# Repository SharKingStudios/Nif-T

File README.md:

# Nif-T - An all in one smart home automation board

### A No-Nonsense Ethernet + PoE Smart-Home Controller

---

## Renders  
*Visuals because everyone loves eye candy.*

> *The middle ground planes are hidden in the PCB Routing render*

---

## BOM  
All the silicon, magnetics, and clicky-relay goodness live **[here](/BOM.csv)**.

**Main characters:**
- **MCU:** ESP32-WROOM-32E
- **Ethernet PHY:** LAN8720A (RMII, external 50 MHz oscillator)
- **Power over Ethernet:** IEEE 802.3af PoE (on-board PD + isolation)
- **Relays:** 8× PCB-mount power relays
- **RGB LEDs:** 10× SK6812 Mini
- **Buzzer:** On-board piezo
- **User Input:** Programmable user button
- **Connectivity:** Ethernet (primary), USB-UART for flashing/debug
- **Power:** PoE-powered with on-board regulation for ESP32 + peripherals
- **Misc:** Boot circuitry, reset logic, pull-ups, decoupling, and other necessary magic

(See `BOM.md` for full part values, footprints, and sourcing.)

---

## What is this?

**Nif-T** is a **wired smart-home automation controller** built around an **ESP32-WROOM-32E**, designed to be the thing that actually flips real switches when you ask your house to do something.

It’s meant for:
- **Lights**
- **Outlets**
- **Relays**
- **Buzzers**
- **Addressable LEDs**
- And other “turn this on when I say so” tasks

Unlike a lot of Wi-Fi-only smart devices, **Nif-T speaks Ethernet** — and it can be powered over the same cable using **PoE**. One cable in, automation out.

At a high level, Nif-T:
- Exposes **physical relays and LEDs**
- Talks to **Home Assistant**
- Which then talks to **Google Home**
- So you can say things like:

> *“Hey Google, turn on the big light.”*

…and something actually happens.

---

## Features

### Relay Control
- **8× independent relay outputs**
- Designed for:
  - Lighting circuits
  - Power control
  - Low-voltage automation tasks
- Each relay is individually addressable via firmware
- Can be controlled via:
  - MQTT
  - Home Assistant
  - Google Home (through HA)

*(Please don’t hot-switch mains unless you know what you’re doing.)*

---

### Ethernet + PoE
Because reliability matters — and wall warts are annoying.

- **LAN8720A Ethernet PHY**
  - RMII interface
  - Dedicated 50 MHz oscillator on the PHY
- **IEEE 802.3af Power over Ethernet**
  - Single-cable power + data
  - On-board PD controller and isolation
  - Clean DC rails generated locally
- No Wi-Fi congestion
- No random disconnects
- No external power brick required

Plug in Ethernet. That’s it.

---

### RGB Status LEDs
Because silent boards are boring.

- **10× SK6812 Mini (GRBW) LEDs**
- Can indicate:
  - Network status
  - MQTT / Home Assistant connection
  - Relay activity
  - Boot / error states
  - Or just run rainbow animations for morale
- Fully firmware-controlled

---

### Buttons & Feedback
- **User button**
  - Can be mapped to:
    - Toggle a relay
    - Enter config mode
    - Trigger a scene
- **On-board buzzer**
  - Boot beeps
  - Error alerts
  - Confirmation chirps
  - Mildly annoying sounds (optional but encouraged)

---

## Connectivity & IO

- **ESP32-WROOM-32E**
  - Dual-core MCU
  - Plenty of GPIO for:
    - Relays
    - LEDs
    - Buttons
    - Buzzers
- **USB-UART**
  - Firmware flashing
  - Serial debugging
- **Screw terminals**
  - For relays and power connections that shouldn’t wiggle loose

---

## Pin Highlights (High-Level)

| Function        | Notes                                   |
|-----------------|------------------------------------------|
| Relays          | 8× GPIO-controlled outputs               |
| LED Data        | SK6812 GRBW strip (10 LEDs)              |
| Ethernet RMII   | LAN8720A w/ external 50 MHz oscillator   |
| PoE Input       | IEEE 802.3af compliant                   |
| User Button     | Input-only GPIO (external pull-ups)      |
| Buzzer          | GPIO-driven piezo output                 |

*(See schematic for full pin mapping and signal names.)*

---

## How It Works

At a high level:

1. **You plug in Ethernet** (which also provides power via PoE)
2. The **PoE PD negotiates power** and generates isolated DC rails
3. The **ESP32 boots** and brings up Ethernet
4. It connects to:
   - An **MQTT broker** (usually Home Assistant)
5. Home Assistant:
   - Discovers Nif-T automatically
   - Exposes relays and LEDs as entities
6. Google Home talks to Home Assistant
7. You talk to Google
8. Nif-T clicks relays and blinks LEDs

---

## Example Use Cases

- “Hey Google, turn on the **workbench lights**”
- “Turn off **everything downstairs**”
- LED status strip that shows:
  - Green = online
  - Red = offline
  - Blue = updating
- Physical button toggles a relay *and* triggers a Home Assistant scene
- Buzzer chirps when automations fire (or silently if you prefer)

---

## Why?

Because:
- Wi-Fi smart plugs are flaky
- Ethernet is king
- PoE makes installs clean
- And sometimes you just want a **solid, hackable, relay board** that plays nicely with modern home automation

Nif-T exists to be:
- Boring in the best way
- Reliable
- Predictable
- And extremely easy to integrate into a real automation stack

---

## Contribute

Ideas, improvements, and constructive roasting welcome.

- Open an **issue**
- Submit a **PR**
- Suggest features
- Argue about relay counts

---

## Disclaimer

This project is open-source, built for fun, and tested only in theory.

If you:
- Wire mains incorrectly
- Ignore clearance rules
- Overload a relay
- Or let the magic smoke out

That’s on you.

Be careful, be smart, and enjoy having a house that actually listens.

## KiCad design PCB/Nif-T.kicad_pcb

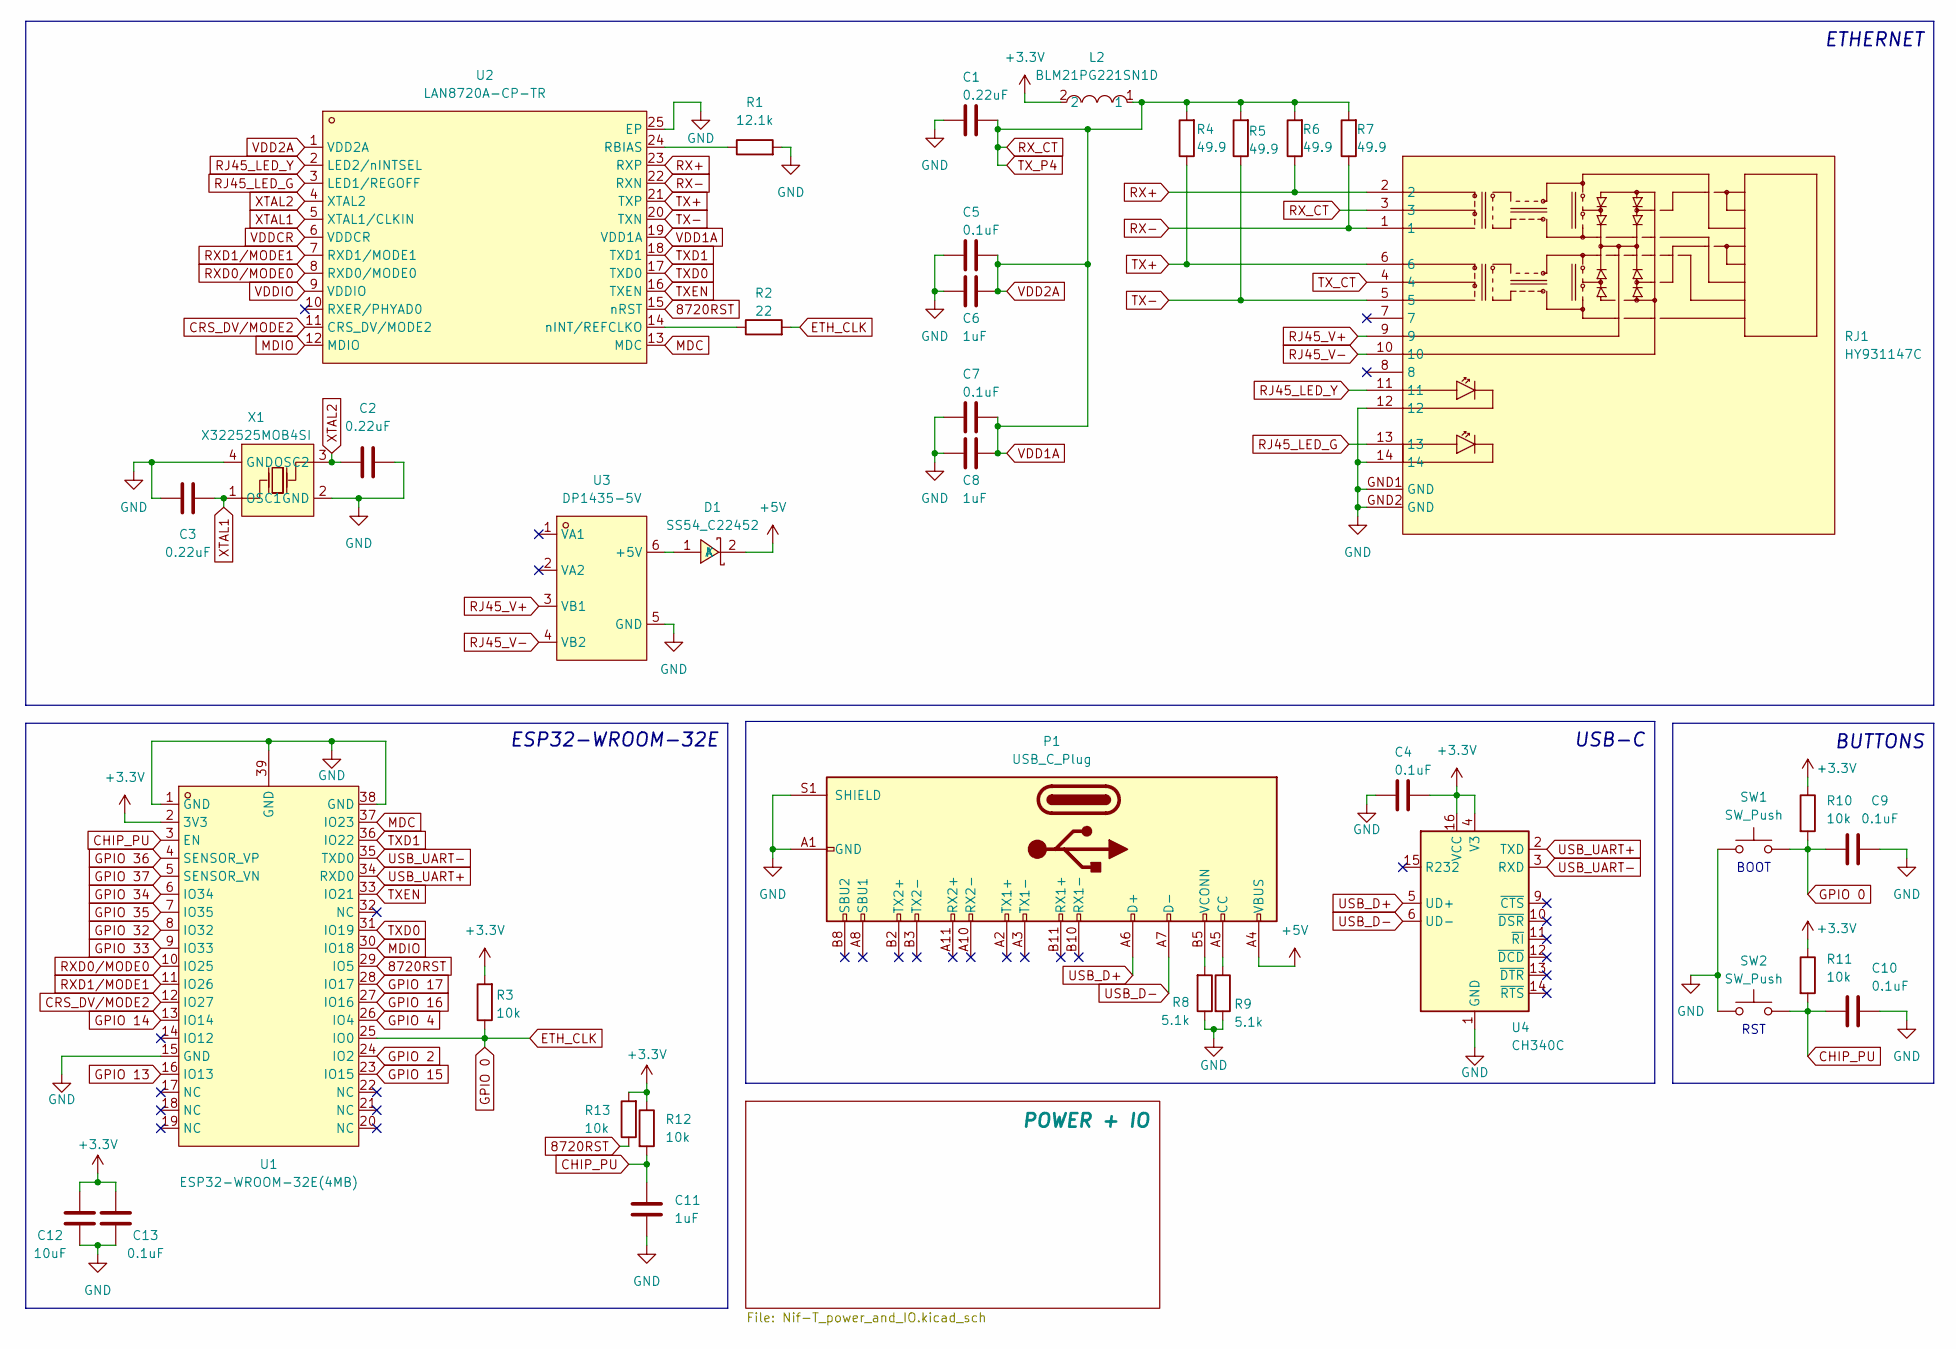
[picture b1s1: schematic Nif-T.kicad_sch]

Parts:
C1, C2, C3: 0.22uF; C0805
C4, C5, C7, C9, C10, C13: 0.1uF; C0805
C6, C8, C11: 1uF; C0805
C12: 10uF; C0805
D1: SS54_C22452; SMA_L4.4-W2.8-LS5.4-R-RD; LCSC Part C22452
L2: BLM21PG221SN1D; L0805; LCSC Part C85840
P1: USB_C_Plug; USB-C_SMD-TYPE-C-31-M-12
R1: 12.1k; R0805
R2: 22; R0805
R3, R10, R11, R12, R13: 10k; R0805
R4, R5, R6, R7: 49.9; R0805
R8, R9: 5.1k; R0805
RJ1: HY931147C; RJ45-TH_HY931147C; LCSC Part C91754
SW1, SW2: SW_Push; SW-SMD_L3.9-W3.0-P4.45
U1: ESP32-WROOM-32E(4MB); WIFI-SMD_ESP32-WROOM-32E; LCSC Part C701341
U2: LAN8720A-CP-TR; QFN-24_L4.0-W4.0-P0.50-BL-EP2.6; LCSC Part C45223
U3: DP1435-5V; PWRM-TH_DP1435-XX; LCSC Part C5380097
U4: CH340C; SOIC-16_3.9x9.9mm_P1.27mm
X1: X322525MOB4SI; CRYSTAL-SMD_4P-L3.2-W2.5-BL; LCSC Part C9006

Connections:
8720RST: R13.1, U1.29 (IO5), U2.15 (nRST)
+3.3V: C4.1, C12.2, C13.2, L2.2, R3.2, R10.1, R11.1, R12.1, R13.2, U1.2 (3V3), U4.4 (V3), U4.16 (VCC); also elsewhere on the board
+5V: D1.2 (K), P1.A4 (VBUS), P1.A9 (VBUS), P1.B4 (VBUS), P1.B9 (VBUS); also elsewhere on the board
CHIP_PU: C10.1, C11.1, R11.2, R12.2, SW2.1, U1.3 (EN)
CRS_DV/MODE2: U1.12 (IO27), U2.11 (CRS_DV/MODE2)
ETH_CLK: C9.1, R2.2, R3.1, R10.2, SW1.1, U1.25 (IO0)
GND: C1.2, C2.2, C3.1, C4.2, C5.2, C6.2, C7.2, C8.2, C9.2, C10.2, C11.2, C12.1, C13.1, P1.A1 (GND), P1.A12 (GND), P1.B1 (GND), P1.B12 (GND), P1.S1 (SHIELD), R1.2, R8.1, R9.2, RJ1.12, RJ1.14, RJ1.GND1 (GND), RJ1.GND2 (GND), SW1.2, SW2.2, U1.1 (GND), U1.15 (GND), U1.38 (GND), U1.39 (GND), U2.25 (EP), U3.5 (GND), U4.1 (GND), X1.2 (GND), X1.4 (GND); also elsewhere on the board
GPIO 2: U1.24 (IO2); also elsewhere on the board
GPIO 4: U1.26 (IO4); also elsewhere on the board
GPIO 13: U1.16 (IO13); also elsewhere on the board
GPIO 14: U1.13 (IO14); also elsewhere on the board
GPIO 15: U1.23 (IO15); also elsewhere on the board
GPIO 16: U1.27 (IO16); also elsewhere on the board
GPIO 17: U1.28 (IO17); also elsewhere on the board
GPIO 32: U1.8 (IO32); also elsewhere on the board
GPIO 33: U1.9 (IO33); also elsewhere on the board
GPIO 34: U1.6 (IO34); also elsewhere on the board
GPIO 35: U1.7 (IO35); also elsewhere on the board
GPIO 36: U1.4 (SENSOR_VP); also elsewhere on the board
GPIO 37: U1.5 (SENSOR_VN); also elsewhere on the board
MDC: U1.37 (IO23), U2.13 (MDC)
MDIO: U1.30 (IO18), U2.12 (MDIO)
unnamed: D1.1 (A), U3.6 (+5V)
unnamed: P1.A5 (CC), R9.1
unnamed: P1.B5 (VCONN), R8.2
unnamed: R1.1, U2.24 (RBIAS)
unnamed: R2.1, U2.14 (nINT/REFCLKO)
RJ45_LED_G: RJ1.13, U2.3 (LED1/REGOFF)
RJ45_LED_Y: RJ1.11, U2.2 (LED2/nINTSEL)
RJ45_V+: RJ1.9, U3.3 (VB1)
RJ45_V-: RJ1.10, U3.4 (VB2)
RX+: R6.1, RJ1.2, U2.23 (RXP)
RX-: R7.1, RJ1.1, U2.22 (RXN)
RXD0/MODE0: U1.10 (IO25), U2.8 (RXD0/MODE0)
RXD1/MODE1: U1.11 (IO26), U2.7 (RXD1/MODE1)
RX_CT: C1.1, C5.1, C6.1, C7.1, C8.1, L2.1, R4.2, R5.2, R6.2, R7.2, RJ1.3, U2.1 (VDD2A), U2.19 (VDD1A)
TX+: R4.1, RJ1.6, U2.21 (TXP)
TX-: R5.1, RJ1.5, U2.20 (TXN)
TXD0: U1.31 (IO19), U2.17 (TXD0)
TXD1: U1.36 (IO22), U2.18 (TXD1)
TXEN: U1.33 (IO21), U2.16 (TXEN)
TX_CT: RJ1.4
USB_D+: P1.A6 (D+), U4.5 (UD+)
USB_D-: P1.A7 (D-), U4.6 (UD-)
USB_UART+: U1.34 (RXD0), U4.2 (TXD)
USB_UART-: U1.35 (TXD0), U4.3 (RXD)
VDDCR: U2.6 (VDDCR)
VDDIO: U2.9 (VDDIO)
XTAL1: C3.2, U2.5 (XTAL1/CLKIN), X1.1 (OSC1)
XTAL2: C2.1, U2.4 (XTAL2), X1.3 (OSC2)

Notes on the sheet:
BOOT
ESP32-WROOM-32E
ETHERNET
RST
USB-C
BUTTONS

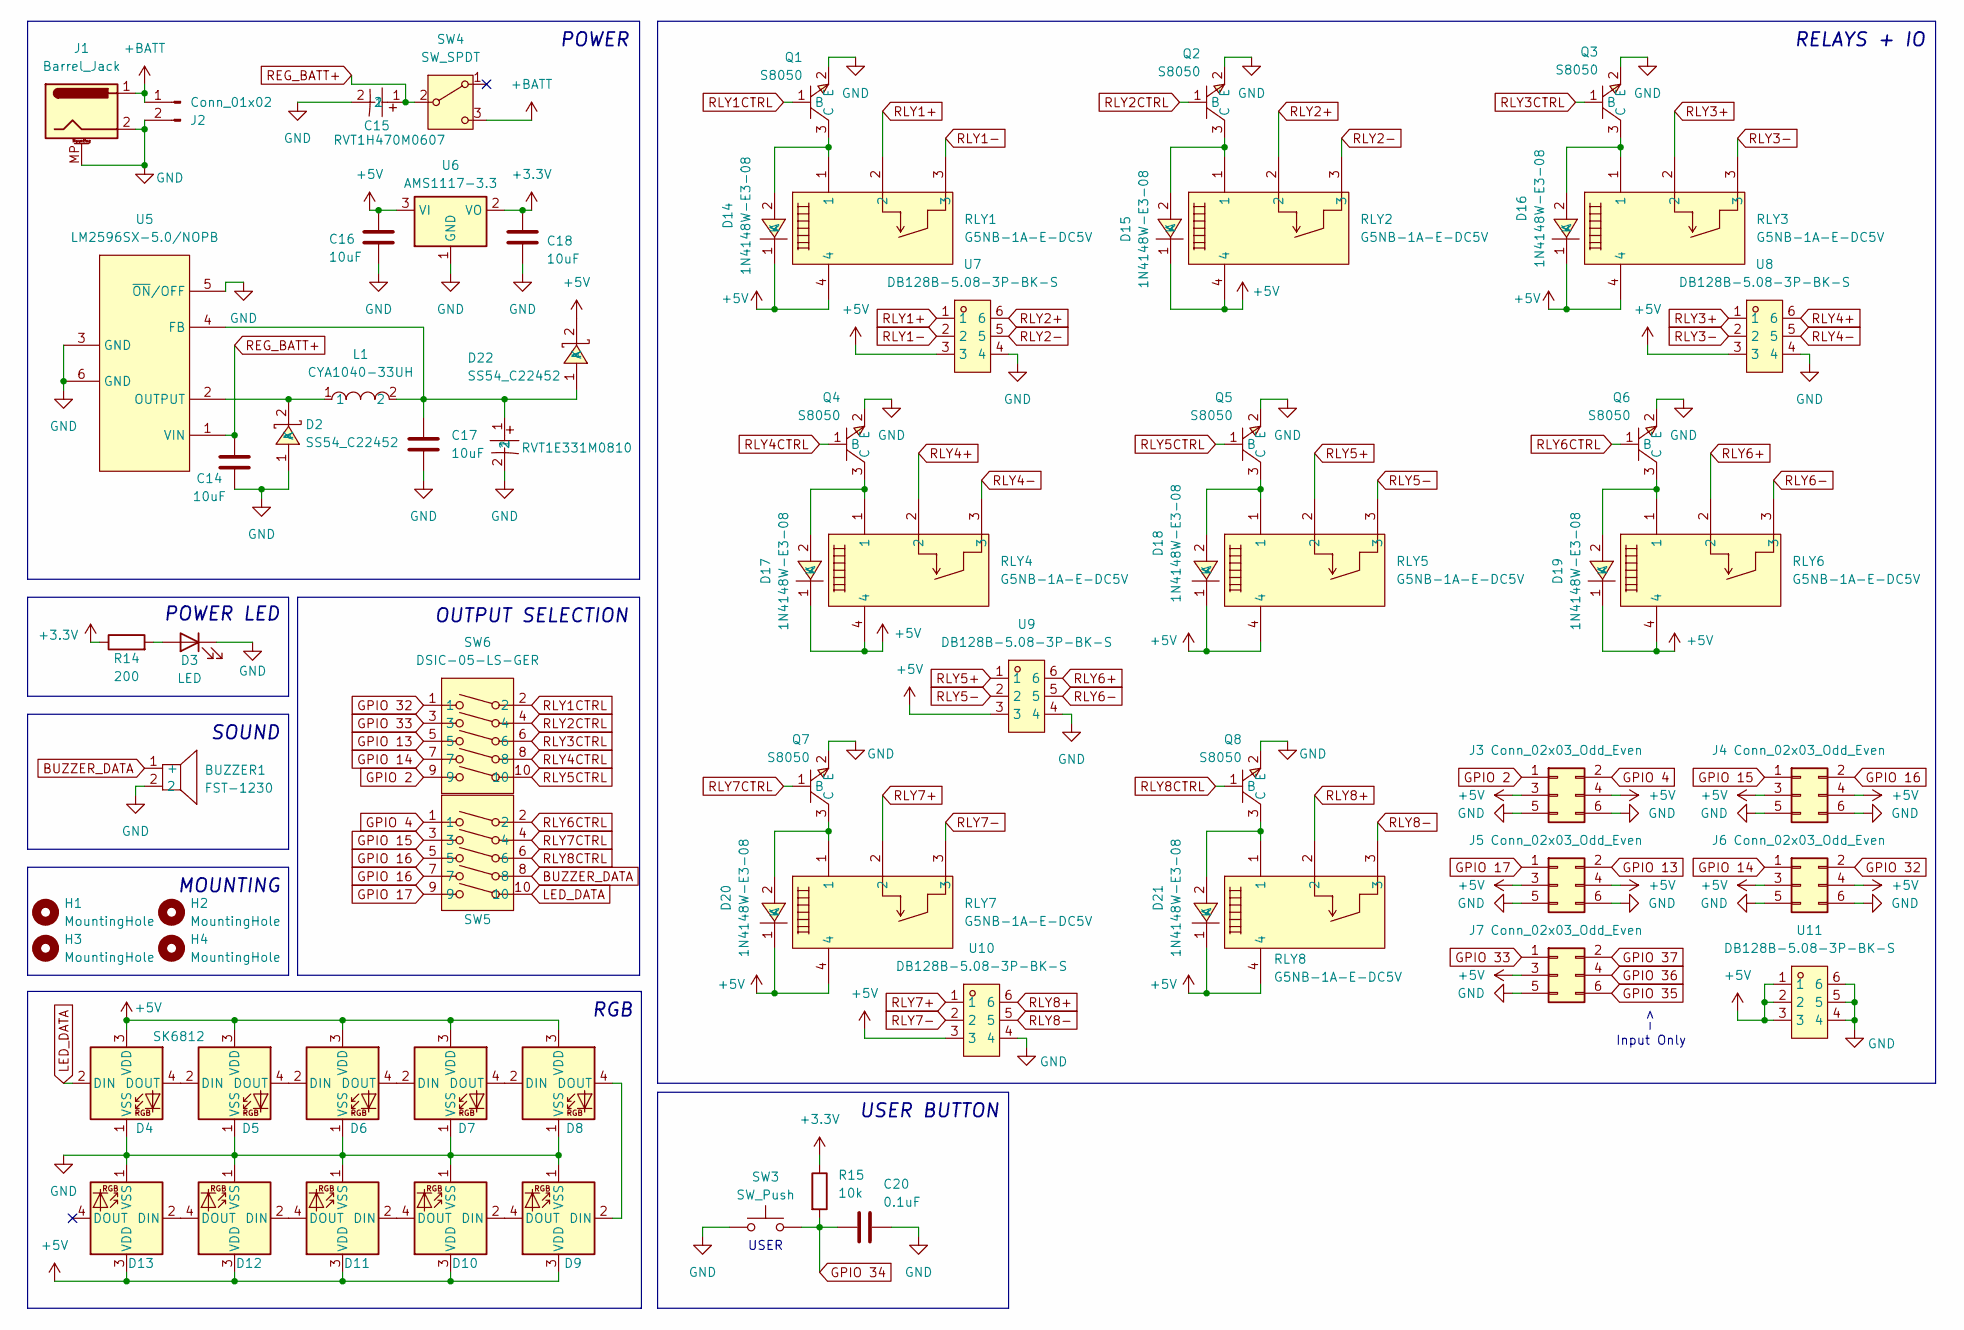
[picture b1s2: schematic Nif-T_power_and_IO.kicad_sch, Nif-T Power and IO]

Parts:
BUZZER1: FST-1230; BUZ-SMD_L12.0-W12.0_FUET-1230; LCSC Part C391037
C14, C16, C17, C18: 10uF; C0805
C15: RVT1H470M0607; CAP-SMD_BD6.3-L6.6-W6.6-LS7.6-FD; LCSC Part C72523
C19: RVT1E331M0810; CAP-SMD_BD8.0-L8.3-W8.3-LS9.3-FD-1; LCSC Part C335985
C20: 0.1uF; C0805
D2, D22: SS54_C22452; SMA_L4.4-W2.8-LS5.4-R-RD; LCSC Part C22452
D3: LED; LED0805-RD
D4, D5, D6, D7, D8, D9, D10, D11, D12, D13: SK6812; LED_SK6812_PLCC4_5.0x5.0mm_P3.2mm
D14, D15, D16, D17, D18, D19, D20, D21: 1N4148W-E3-08; SOD-123_L2.8-W1.8-LS3.7-RD; LCSC Part C241939
H1, H2, H3, H4: MountingHole; MountingHole_3.2mm_M3_Pad_Via
J1: Barrel_Jack; DC-IN-TH_DC-005-A200
J2: Conn_01x02; CONN-TH_P5.00_KF301-5.0-2P
J3, J4, J5, J6, J7: Conn_02x03_Odd_Even; HDR-SMD_6P-P2.54-V
L1: CYA1040-33UH; IND-SMD_L11.6-W10.1; LCSC Part C6364680
Q1, Q2, Q3, Q4, Q5, Q6, Q7, Q8: S8050; SOT-23-3_L2.9-W1.3-P1.90-LS2.4-BR; LCSC Part C916390
R14: 200; R0805
R15: 10k; R0805
RLY1, RLY2, RLY3, RLY4, RLY5, RLY6, RLY7, RLY8: G5NB-1A-E-DC5V; RELAY-TH_G5NB-1A-E-DCXX; LCSC Part C48746
SW3: SW_Push; SW-SMD_L3.9-W3.0-P4.45
SW4: SW_SPDT; SW-SMD_MST-12D18G4-SPDT-SLIDE-SWITCH
SW5, SW6: DSIC-05-LS-GER; SW-SMD_DSIC-05-LS-GER; LCSC Part C7471367
U5: LM2596SX-5.0/NOPB; TO-263-5_L10.2-W8.9-P1.70-TL; LCSC Part C10002
U6: AMS1117-3.3; SOT-223-3_TabPin2
U7, U8, U9, U10, U11: DB128B-5.08-3P-BK-S; CONN-TH_DB128B-5.08-3P-XX-S; LCSC Part C500038

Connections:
+3.3V: C18.1, R14.1, R15.1, U6.2 (VO); also elsewhere on the board
+5V: C16.1, D4.3 (VDD), D5.3 (VDD), D6.3 (VDD), D7.3 (VDD), D8.3 (VDD), D9.3 (VDD), D10.3 (VDD), D11.3 (VDD), D12.3 (VDD), D13.3 (VDD), D14.1 (K), D15.1 (K), D16.1 (K), D17.1 (K), D18.1 (K), D19.1 (K), D20.1 (K), D21.1 (K), D22.2 (K), J3.3, J3.4, J4.3, J4.4, J5.3, J5.4, J6.3, J6.4, J7.3, RLY1.4, RLY2.4, RLY3.4, RLY4.4, RLY5.4, RLY6.4, RLY7.4, RLY8.4, U6.3 (VI), U7.3, U8.3, U9.3, U10.3, U11.1, U11.2, U11.3; also elsewhere on the board
+BATT: J1.1, J2.1, SW4.3 (C)
BUZZER_DATA: BUZZER1.1 (+), SW5.8
GND: BUZZER1.2, C14.1, C15.2, C16.2, C17.2, C18.2, C19.2, C20.2, D2.1 (A), D3.1 (K), D4.1 (VSS), D5.1 (VSS), D6.1 (VSS), D7.1 (VSS), D8.1 (VSS), D9.1 (VSS), D10.1 (VSS), D11.1 (VSS), D12.1 (VSS), D13.1 (VSS), J1.2, J1.MP (MountPin), J2.2, J3.5, J3.6, J4.5, J4.6, J5.5, J5.6, J6.5, J6.6, J7.5, Q1.2 (E), Q2.2 (E), Q3.2 (E), Q4.2 (E), Q5.2 (E), Q6.2 (E), Q7.2 (E), Q8.2 (E), SW3.2, U5.3 (GND), U5.5 (~ON/OFF), U5.6 (GND), U6.1 (GND), U7.4, U8.4, U9.4, U10.4, U11.4, U11.5, U11.6; also elsewhere on the board
GPIO 2: J3.1, SW6.9; also elsewhere on the board
GPIO 4: J3.2, SW5.1; also elsewhere on the board
GPIO 13: J5.2, SW6.5; also elsewhere on the board
GPIO 14: J6.1, SW6.7; also elsewhere on the board
GPIO 15: J4.1, SW5.3; also elsewhere on the board
GPIO 16: J4.2, SW5.5, SW5.7; also elsewhere on the board
GPIO 17: J5.1, SW5.9; also elsewhere on the board
GPIO 32: J6.2, SW6.1; also elsewhere on the board
GPIO 33: J7.1, SW6.3; also elsewhere on the board
GPIO 34: C20.1, R15.2, SW3.1; also elsewhere on the board
GPIO 35: J7.6; also elsewhere on the board
GPIO 36: J7.4; also elsewhere on the board
GPIO 37: J7.2; also elsewhere on the board
LED_DATA: D4.2 (DIN), SW5.10
unnamed: D2.2 (K), L1.1, U5.2 (OUTPUT)
unnamed: D3.2 (A), R14.2
unnamed: D4.4 (DOUT), D5.2 (DIN)
unnamed: D5.4 (DOUT), D6.2 (DIN)
unnamed: D6.4 (DOUT), D7.2 (DIN)
unnamed: D7.4 (DOUT), D8.2 (DIN)
unnamed: D8.4 (DOUT), D9.2 (DIN)
unnamed: D9.4 (DOUT), D10.2 (DIN)
unnamed: D10.4 (DOUT), D11.2 (DIN)
unnamed: D11.4 (DOUT), D12.2 (DIN)
unnamed: D12.4 (DOUT), D13.2 (DIN)
unnamed: D14.2 (A), Q1.3 (C), RLY1.1
unnamed: D15.2 (A), Q2.3 (C), RLY2.1
unnamed: D16.2 (A), Q3.3 (C), RLY3.1
unnamed: D17.2 (A), Q4.3 (C), RLY4.1
unnamed: D18.2 (A), Q5.3 (C), RLY5.1
unnamed: D19.2 (A), Q6.3 (C), RLY6.1
unnamed: D20.2 (A), Q7.3 (C), RLY7.1
unnamed: D21.2 (A), Q8.3 (C), RLY8.1
unnamed: C17.1, C19.1, D22.1 (A), L1.2, U5.4 (FB)
REG_BATT+: C14.2, C15.1, SW4.2 (B), U5.1 (VIN)
RLY1+: RLY1.2, U7.1
RLY1-: RLY1.3, U7.2
RLY1CTRL: Q1.1 (B), SW6.2
RLY2+: RLY2.2, U7.6
RLY2-: RLY2.3, U7.5
RLY2CTRL: Q2.1 (B), SW6.4
RLY3+: RLY3.2, U8.1
RLY3-: RLY3.3, U8.2
RLY3CTRL: Q3.1 (B), SW6.6
RLY4+: RLY4.2, U8.6
RLY4-: RLY4.3, U8.5
RLY4CTRL: Q4.1 (B), SW6.8
RLY5+: RLY5.2, U9.1
RLY5-: RLY5.3, U9.2
RLY5CTRL: Q5.1 (B), SW6.10
RLY6+: RLY6.2, U9.6
RLY6-: RLY6.3, U9.5
RLY6CTRL: Q6.1 (B), SW5.2
RLY7+: RLY7.2, U10.1
RLY7-: RLY7.3, U10.2
RLY7CTRL: Q7.1 (B), SW5.4
RLY8+: RLY8.2, U10.6
RLY8-: RLY8.3, U10.5
RLY8CTRL: Q8.1 (B), SW5.6

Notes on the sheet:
POWER LED
OUTPUT SELECTION
SOUND
RELAYS + IO
USER
RGB
USER BUTTON
MOUNTING
POWER
Input Only

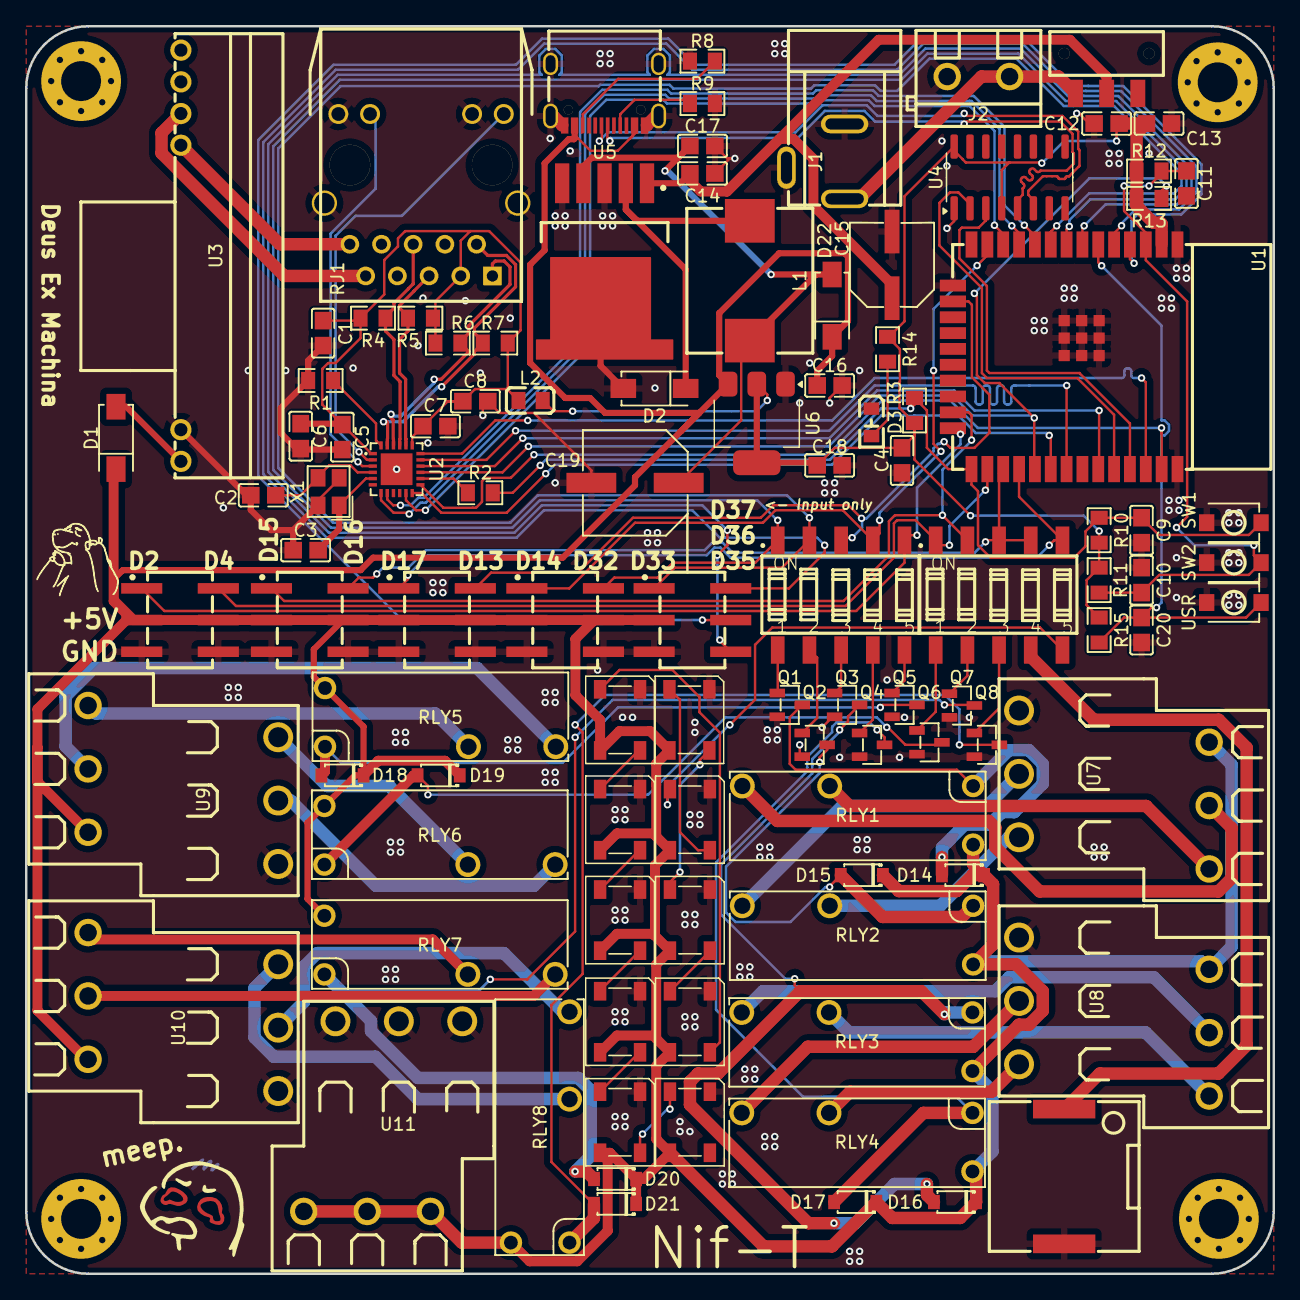
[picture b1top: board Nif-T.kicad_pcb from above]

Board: 4 copper layers, 100.0 x 100.0 mm, 107 parts (0 on the bottom side), 95 nets.

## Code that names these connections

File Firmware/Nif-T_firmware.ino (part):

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static const bool RELAY_ACTIVE_LOW = false;

// Relay 8 shares GPIO16 with buzzer.
// Set this true if GPIO16 is BUZZER_DATA, not relay8:
static const bool USE_GPIO16_AS_BUZZER = false;

// -------------------- PIN MAP (from your message) --------------------
// Ethernet PHY (LAN8720A)
static const int PIN_ETH_POWER_OR_RESET = 5;  // IO5 8720RST (Arduino ETH uses this as "power pin" toggle)
static const int PIN_ETH_MDC = 23;            // IO23 MDC
static const int PIN_ETH_MDIO = 18;           // IO18 MDIO
static const int PIN_ETH_ADDR = 0;            // common LAN8720 phy addr is 0 (sometimes 1)

// Ethernet MAC pins you listed (handled internally by ESP-IDF):
// GPIO19 TXD0
// GPIO22 TXD1
// GPIO21 TXEN
// GPIO25 RXD0 / MODE0
// GPIO26 RXD1 / MODE1
// GPIO27 CRS_DV / MODE2
// Clock: GPIO0 ETH_CLK + BOOT (we use ETH_CLOCK_GPIO0_IN)

// Relays
static const int PIN_RLY1 = 32;
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static const int PIN_RLY8 = 16; // unless USE_GPIO16_AS_BUZZER

// LEDs
static const int PIN_LED_DATA = 17;
static const int LED_COUNT = 10;

// User button (GPIO34 is input-only; typically needs external pullup/pulldown)
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WiFiClient netClient;          // Works with ETH as well on ESP32 Arduino core
PubSubClient mqtt(netClient);

Adafruit_NeoPixel strip(LED_COUNT, PIN_LED_DATA, NEO_GRBW + NEO_KHZ800);

String baseTopic;              // nif-t/<chipid>
String deviceName;             // nif-t-<chipid>
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
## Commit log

2025-11-26 Added Components
2025-11-28 Big ol trip
    Worked on this while traveling.
2025-12-05 PCB Reconfigured and Rerouted
2025-12-12 Add Nif-T ESP32 firmware
    Added initial Nif-T_firmware.ino for ESP32-WROOM-32E with LAN8720A Ethernet, MQTT relay/LED control, and Home Assistant discovery.
2025-12-12 Add README and PCB Renders
2025-12-13 BOM and Gerbers Done
2025-12-18 Impedance matching and 4 layers
    The PCB is now a 4 layer board for better ground pour coverage and to allow for proper impedance matching as needed by ethernet.
    PCB Toolkit was used to calculate the new widths needed for proper ethernet trace impedance.
2025-12-31 Updated Gerbers
2026-04-01 New Firmware
